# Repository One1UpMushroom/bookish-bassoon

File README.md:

# LED Task Lamp Controller

Firmware and a driver board for a five-channel LED task lamp (red, green, blue, warm
white, cool white), built from two 24 V LED strips and Adafruit breakout boards, and
controlled by a single push-button rotary encoder and a 240×240 color display.

| Part | Role |
|---|---|
| Adafruit **QT Py RP2040** | Microcontroller. Dual-core, 8 hardware PWM slices, 8 MB flash |
| Adafruit **I2C QT rotary encoder** (seesaw; PID 4991, or 5880 pre-soldered) | Encoder, push switch and an RGB "locator" pixel, all over I2C |
| Adafruit **240×240 TFT** (ST7789) | User interface |
| 1 m tunable-white strip (2700 K + 6500 K) and 0.8 m RGB strip, both 24 V | The light: about 15 W of white and 9 W of colour |
| **Driver board** ([`hardware/`](hardware/README.md)) | Carries the QT Py, makes its 5 V from the 24 V supply, and switches each strip colour with a MOSFET |

---

## 1. Wiring

```
                          QT Py RP2040
                   ┌─────────────────────────┐
     Red gate  ◄── │ A0  (GP29)    5V        │◄── 5 V from the board's buck converter
   Green gate  ◄── │ A1  (GP28)    GND       │── common ground
    Blue gate  ◄── │ A2  (GP27)    3V        │── TFT Vin, (encoder via STEMMA)
    Warm gate  ◄── │ A3  (GP26)    MO (GP3)  │──► TFT MOSI (SI)
     TFT TCS   ◄── │ SDA (GP24)    MI (GP4)  │◄── Encoder INT (extra wire)
     TFT D/C   ◄── │ SCL (GP25)    SCK (GP6) │──► TFT SCK
    Cool gate  ◄── │ TX  (GP20)    RX (GP5)  │──► TFT Lite (backlight PWM)
                   │   [STEMMA QT port]──────│──► Rotary encoder breakout
                   └─────────────────────────┘
```

| QT Py pad | GPIO | Connects to | Notes |
|---|---|---|---|
| A0 | GP29 | Red MOSFET gate (through 220 Ω) | PWM slice 6B |
| A1 | GP28 | Green MOSFET gate | PWM slice 6A |
| A2 | GP27 | Blue MOSFET gate | PWM slice 5B |
| A3 | GP26 | Warm white MOSFET gate | PWM slice 5A |
| TX | GP20 | Cool white MOSFET gate | PWM slice 2A |
| RX | GP5 | TFT **Lite** | PWM slice 2B: dimmable backlight |
| SCK | GP6 | TFT **SCK** | SPI0 |
| MO | GP3 | TFT **SI / MOSI** | SPI0 |
| MI | GP4 | Encoder breakout **INT** pad | Optional extra wire. Lets the firmware skip I2C reads while the knob is idle |
| SDA | GP24 | TFT **TCS** | Used as a plain GPIO |
| SCL | GP25 | TFT **D/C** | Used as a plain GPIO |
| STEMMA QT | GP22/23 | Encoder breakout | I2C1 (`Wire1`), 400 kHz |
| 3V / GND | | TFT Vin / GND | |
| 5V | | The board's 5 V buck converter (LMR33630), through a diode | USB may be connected at the same time |
| – | – | TFT **RST**, **CCS**, **SO**, **TE** | Leave unconnected. The display resets itself at power-up, and the microSD slot isn't used (leave it empty) |

On the driver board the LED pins and the 5 V feed are copper. The only wires are the
eight from the board's **J4** header (seven to the TFT, one to the encoder's INT pad),
the encoder's STEMMA QT cable, the 24 V supply and the two strips.

This uses all 11 pads, and every LED channel gets its own hardware PWM output.
If you don't run the INT wire, the firmware notices within a couple of knob turns and
falls back to plain polling. The pin
choice is deliberate: R+G and B+WW share PWM slices, so the firmware can phase-offset
them (see §5). Pin numbers live in `firmware/TaskLamp/config.h`.

**Encoder and I2C notes (from the Adafruit guides):**
* Clockwise turns increase values. The breakout's 45° encoder counts backwards, and the
  firmware compensates. *Settings ▸ Knob dir* flips it if your encoder differs.
* Touching the back of the encoder board can register as a button press. Insulate it
  from fingers and metal in the enclosure.
* Keep the STEMMA QT cable short (about 15 cm or less). Plug it in before powering up:
  I2C isn't designed for hot-plugging, although the firmware does retry every 2 s.
* With several encoders on one cable, Adafruit suggests powering their VIN separately
  if they misbehave.

**More controls without more pins:** the STEMMA QT port can be daisy-chained. A
**second rotary encoder breakout** with its A0 jumper cut (address 0x37) is detected
automatically. It becomes a dedicated **brightness knob**, and its click becomes
**power on/off**, working from any screen. This is the most worthwhile add-on for
day-to-day use. (The second knob has no INT wire, so it's simply polled.)

---

## 2. The driver board

The strips are never driven from the GPIO pins. The board in
[`hardware/`](hardware/README.md) does that, and also powers the QT Py from the lamp's
24 V supply:

* **24 V input**: a 2 A fuse, a Schottky diode against a supply wired backwards, a TVS
  diode against spikes, and bulk capacitors.
* **5 V for the QT Py** from an LMR33630 buck converter on the board (the BUCK//33630
  circuit), through a diode to the 5V pad. The 24 V input is the board's only power input.
  USB can be plugged in while the lamp is powered.
* **Five identical switches**: a logic-level MOSFET per colour (IRLB8721), its gate driven
  straight from the QT Py pin through 220 Ω, a 100 kΩ pull-down, and a 1N5819 from the
  strip wire back to +24 V.

`hardware/README.md` has the schematic, the files to send to PCBWay, the build order and
the power-up checks. [`docs/driver-build.html`](docs/driver-build.html) is the same build
as a step-by-step picture booklet. The parts not already in the inventory are listed with
links in [`docs/parts-to-order.md`](docs/parts-to-order.md).

What the firmware assumes about that hardware:

* **A high pin means light.** Each pin switches its MOSFET on directly.
* **The pull-downs keep the lamp dark** whenever the pins are not driven: during reset,
  in USB bootloader mode, or with the QT Py unplugged. The firmware then fades in rather
  than switching on hard.
* **PWM frequency.** The default is 2 kHz, under *Settings ▸ PWM freq* (500 Hz to 20 kHz).
  Lower frequencies dim further down; higher ones move any flicker beyond what a camera
  picks up. Resolution depends on frequency and on the CPU speed chosen in the Tools
  menu: 15–16 bits at 2 kHz, about 13 bits at 20 kHz.
* **The bottom of the dimming range.** A MOSFET gate driven through a resistor needs a
  fraction of a microsecond before the strip lights, so the very shortest pulses give no
  light. *Min duty* (§4) sets where light starts; the default is an estimate.
* **Currents.** The defaults are the catalogue figures for these strips: about 0.13 A per
  RGB colour and 0.30 A per white, 1.0 A with everything at 100 %.
* **The 3V rail** (QT Py regulator, 500 mA available) feeds the TFT and the encoder,
  tens of mA in total.
* **Display glass:** the 1.54" panel's backlight can slowly peel away from the TFT if
  nothing holds it. Plan a clear cover or window in the enclosure (or tape the edges).

---

## 3. Building and flashing

**Arduino IDE**
1. Boards Manager: install **Raspberry Pi Pico/RP2040** by Earle F. Philhower III.
2. Board: **Adafruit QT Py RP2040** (not the *Picoprobe* or *pico-debug* variants).
   *Flash Size*: pick an option **with** a filesystem (FS) of at least 64 KB. The default,
   "8MB (no FS)", leaves nowhere to store settings; the lamp then shows "No flash FS:
   settings not saved" on the home screen.
3. Library Manager: install **Adafruit seesaw Library**, **Adafruit ST7735 and ST7789 Library**
   and **Adafruit GFX Library**.
4. Open `firmware/TaskLamp/TaskLamp.ino` and upload. If the port doesn't appear, hold
   BOOT, tap RST, and keep holding BOOT until the RPI-RP2 drive appears.

**PlatformIO**: `pio run -t upload` (see `platformio.ini`).

**Host tests** (no hardware needed): `make -C test` runs about 4,100 checks of the
color math, light engine, power limiter, gesture decoder and the whole menu UI, including
a 200,000-event random-input fuzz run under AddressSanitizer/UBSan. `make -C test check`
also type-checks the Arduino-facing files against API stubs.

**Checked against the real toolchain:** the sketch compiles without warnings
(`-Wall -Wextra`) and links into a complete image with arduino-pico 6.3.2 (GCC 16.1),
Adafruit seesaw 1.7.9, Adafruit ST7735 and ST7789 1.12.0, Adafruit GFX 1.13.0 and Adafruit
BusIO 1.17.4. The image is about 392 KB of flash and 22 KB of static RAM.
`tools/rp2040_build_check.sh` repeats that build outside the Arduino IDE.

---

## 4. Using the lamp

### Gestures

| On the **home** screen | |
|---|---|
| **Turn** | Master brightness, 0.1–100 % on a perceptual scale. Steps are finer below 5 %, and spinning faster takes bigger steps |
| **Press + turn** | Quick parameter for the current mode: color temperature (White), hue (Color), speed (Sweep/Flash), period (Breathe/Rainbow), flicker (Candle) |
| **Click** | Open the menu. When the lamp is off: turn on |
| **Double-click** | Cycle through favorites |
| **Hold** (0.6 s) | Lamp on/off, with a smooth fade |

| In **menus** | |
|---|---|
| **Turn** | Move the selection, or change the value while editing |
| **Click** | Open a submenu, start editing a value, or confirm the edit |
| **Hold** | Go back. While editing: cancel and restore the old value |

When the screen is asleep, the first click only wakes it. Turning and holding work
immediately, so you can dim or switch off the lamp in the dark without looking.

### Modes

| Mode | What it does |
|---|---|
| **White** | Color temperature between your warm and cool LEDs, mixed in mired space for even steps |
| **Color** | Hue and saturation. The white part of pastel colors is produced by the white LEDs, which is more efficient and renders color better |
| **Mixer** | All five channels set independently |
| **Sweep** | Up to 8 programmable color steps, each with its own hold and fade time. Repeat, ping-pong or play once; linear or smooth easing; global speed 25–400 % |
| **Flash** | Color A/B flasher: on time, off time, flashes per burst, pause between bursts, speed. Hard-capped at 25 Hz |
| **Breathe** | Slow breathing of the base color, with an adjustable low point |
| **Rainbow** | Continuous hue rotation, with adjustable period and saturation |
| **Candle** | Natural-looking flicker of the base color |

*Breathe* and *Candle* animate the **base color**: the last White/Color/Mixer setting
you used. You can also change it in their *Adjust* menu. While you edit a sweep step or
a flash color, the lamp shows that color live. **Capture light** copies the current
base color into the step.

> ⚠️ Flashing light at 3–30 Hz can trigger seizures in people with photosensitive
> epilepsy. Use the Flash mode with care.

### Menu map

```
Menu
├── Mode ▸ White · Color · Mixer · Sweep · Flash · Breathe · Rainbow · Candle
├── Adjust ▸ (parameters of the current mode; Sweep ▸ Steps ▸ Step n ▸ R G B Warm Cool Hold Fade)
├── Favorites ▸ recall 1-6 · Save current ▸ slot 1-6
├── Sleep: Off / 5 / 15 / 30 / 60 / 90 min / 2 hr (fades out over the last 5 min)
└── Settings
    ├── Transition (fade time for on/off and mode changes)
    ├── White LEDs ▸ Warm LED K · Cool LED K · Max output · Pastel->W
    ├── Display ▸ Brightness · Follow lamp · Timeout · Knob glow
    ├── Knob dir
    ├── Power ▸ Budget · R/G/B/WW/CW current at 100 %
    ├── Channels ▸ Red/Green/Blue/Warm/Cool ▸ Test level · Min duty · Trim
    ├── PWM freq
    ├── Factory reset
    └── Firmware
```

### One-time calibration (recommended)

1. **Channels ▸ each channel**: on this screen the lamp shows *only* that channel at the
   *Test level* (default 0.1 %). Test and preview screens stay up for 10 minutes instead of
   the usual 30 s, so there is time to take a meter reading.
   * Set **Min duty** so the strip just glows at the test level: lower it until the light
     goes out, then back up one step. The defaults (0.12 % for red, 0.16 % for the others)
     come from simulating the driver board. This puts the dimmest real light on the first
     step of the knob.
   * Use **Trim** to cap a channel. This is useful for balancing the warm and cool whites.
2. **White LEDs**: the color temperatures of the warm and cool LEDs. The defaults, 2700 K
   and 6500 K, match the strip in this build.
3. **Power**: the defaults are catalogue figures. Measure each channel's current at 100 %
   and enter it, then set **Budget** to about 80 % of your supply's rating. The home
   screen shows the estimated current draw. Above the budget, all channels are scaled
   down together, so the color stays the same, and the header shows **LIMIT**.
4. **PWM freq**: leave it at 2 kHz unless a camera shows banding (raise it) or you want
   deeper dimming (lower it). Changing it moves the *Min duty* point, so redo step 1.

---

## 5. How the firmware works (and why it's efficient)

```
 core 0 ─ UI ──────────────────────────────┐       core 1 ─ light ───────────────────────────┐
 encoder (I2C, error-checked) → gestures   │       LightEngine: mode/effect → linear RGBWW    │
 → menus/home → Settings + Runtime ────────┼─copy─►  soft start, crossfade, sleep fade        │
 display (banded, change-only)             │       OutputStage: trim → power cap → min duty │
 flash save (debounced, atomic)            │◄──────  PwmBank: 16-bit HW PWM, phase-staggered│
 watchdog (fed only if both cores alive)   │status   backlight glide                         │
```

* **Two cores.** Core 1 does nothing but compute light and write PWM, so fades and
  effects stay smooth while the display redraws. The cores exchange one snapshot each way.
  The mutex is held only for a copy, and core 1 never waits on it. The one thing that does
  pause core 1 is a flash write: the RP2040 can't run code from flash while erasing it, so
  the core is held for a few tens of ms. The hardware PWM keeps running, so a steady light
  shows nothing. See *Flash wear* for how effects are kept clear of it.
* **Perceptual control, linear mixing.** Every level you set is CIE L\* lightness, so
  equal knob steps look equal from 0.1 % to 100 %. Mixing and cross-fading happen in
  linear light, which is how LED light physically adds up.
* **Deep, smooth dimming.** Hardware PWM runs at the highest resolution the chosen
  frequency allows, and the per-channel *Min duty* floor puts the bottom of the knob
  exactly where each strip starts to emit.
* **Less stress on the power supply.** The three PWM slices start a third of a period
  apart, and the second channel in each slice is end-aligned. Channels therefore don't
  all switch on at the same instant, which lowers peak current, ripple and EMI. Every
  on/off and mode change ramps instead of stepping, so there are no inrush spikes. The
  power budget keeps total current inside what your supply can deliver.
* **Low idle power.** The engine ticks at 250 Hz only while something is changing, and
  drops to 50 Hz when the light is steady. PWM registers are written only when a value
  changes. The display is drawn into a 23 KB band buffer, and each band is hashed: bands
  that didn't change are never sent over SPI. A brightness change typically re-sends 1–2
  of the 5 bands. The backlight follows the lamp's brightness (less glare at night),
  dims after the timeout and sleeps 10 s later. The display controller then enters its
  sleep mode. The QT Py's own NeoPixel is left unpowered. When the lamp is off, a faint
  amber glow on the encoder shows where the knob is.
* **Flash wear.** Settings are saved only after 5 s without changes, and only if they
  differ (by CRC) from what's stored. While an effect is running the wait is 30 s, or
  until the light is steady or off, so the short pause a flash write causes doesn't land
  in the middle of a sweep. The write goes through LittleFS (wear-levelled), to
  a temporary file followed by an atomic rename, so a power cut can't corrupt them. On
  load, the data is CRC-checked and every field is range-clamped.
* **Interrupt-driven input.** With INT wired, an idle knob costs one GPIO read per poll.
  I2C is used only when the encoder signals a change, while the button is held, for half
  a second after activity, and in a 4 Hz safety poll. An edge latch catches even short
  INT pulses.
* **Robust input.** Encoder reads check for I2C errors, so a loose cable can't look like
  a held button. A missing encoder is retried every 2 s. The switch is debounced, and the
  hardware watchdog reboots the board if either core ever stalls.
* **Clean power-up.** The backlight is held dark until the first frame is ready, so the
  display's power-up noise is never shown.
* **Display sleep timing.** The ST7789 needs 120 ms between going to sleep and waking, and
  5 ms before its next command. The driver enforces both, so touching the knob at the
  instant the screen dozes off can't leave it dark.

### Source map (`firmware/TaskLamp/`)

| File | Contents | Hardware-free? |
|---|---|---|
| `TaskLamp.ino` | Startup, core 0/core 1 loops, encoder I/O | – |
| `config.h` | Pins and timing | ✓ |
| `color.*` | CIE lightness, HSV, CCT mixing | ✓ |
| `settings.*` | Persistent settings, defaults, sanitizing, CRC, save scheduler | ✓ |
| `engine.*` | Modes, effects, fades, sleep timer, previews | ✓ |
| `output.*` | Trim, power budget, duty floor → PWM levels | ✓ |
| `input.*` | Click / double / long / press-turn gestures, acceleration, INT gating | ✓ |
| `ui.*` | Home screen, menu system, display power policy | ✓ |
| `painter.h` | Drawing interface used by the UI | ✓ |
| `display.*` | ST7789 driver, banded change-only rendering | – |
| `pwm_hw.*` | RP2040 PWM setup and phase staggering | – |
| `storage.*` | LittleFS load/save | – |

Outside the firmware: `hardware/` (the driver board's KiCad project and factory files),
`tools/pcb/` (the generator and checks that produce it) and `tools/rp2040_build_check.sh`
(full build with the real core and libraries).

---

## 6. Status

* All hardware-independent logic is covered by the host tests (`make -C test`).
* The whole sketch builds and links cleanly with the real arduino-pico toolchain and the
  current Adafruit libraries (§3). That was last run on 1.2.0; 1.2.1 changes only default
  values, and the host tests compile it.
* Firmware 1.1 ran on a breadboard build: the display, the encoder and the two white
  channels worked there. **Firmware 1.2.1 has not yet been run on hardware.** It differs
  in its defaults and in dropping one menu option, not in how it drives the pins.
* The driver board passes KiCad's design-rule check, 20 circuit simulations and 22 checks
  of its factory files (`hardware/tasklamp-driver/test-report.md`), but **no board has been
  built yet**. Its power-up section lists
  what to measure on the first one.
* Still worth confirming on the bench:
  * Clockwise turns brighten. If not, use *Knob dir*.
  * The display orientation (`kTftRotation` in `config.h`).
  * INT works: the encoder's red INT LED (on the back) blinks when you turn the knob.
  * No white flash on the display at power-up.

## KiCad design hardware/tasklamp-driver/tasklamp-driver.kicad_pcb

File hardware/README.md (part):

# Task lamp driver board

One circuit board that turns a 24 V supply and a QT Py RP2040 into a five-channel strip
lamp: 0.8 m of RGB tape and 1 m of tunable-white tape, each colour switched by its own
MOSFET.

| | |
|---|---|
| Size | 96.5 × 59 mm, two layers, 1.6 mm |
| Mounting | Four 3.2 mm holes (M3) on a 88.9 × 50.8 mm (3.5 × 2.0 in) rectangle |
| Supply | 24 V DC, 1.5 A or more. About 1.0 A is drawn with every channel at 100 % |
| Outputs | Red, green, blue: about 0.13 A each. Warm white, cool white: about 0.30 A each |
| Controller power | 5 V made on the board from the 24 V input; USB can be plugged in at the same time |
| Parts | Through-hole, except the 5 V converter's eleven surface-mount parts (hand-solderable). Most are in the inventory; fifteen lines to buy ([`docs/parts-to-order.md`](../docs/parts-to-order.md)) |
| Power input | One: 24 V into J1. Everything on the board, the QT Py included, runs from it |

## What is on it

```
 24 V in ─ fuse ─ Schottky ─┬───────────────┬──────────────── +24 V to both strips
          (2 A)  (reverse   │               │
                 protection)│               └─ 5 V buck (LMR33630) ─ diode ─ QT Py 5V pad
                           TVS, 2 × 100 µF

 QT Py pin ── 220 Ω ──┬── gate ┐
                    100 kΩ     │ IRLB8721      × 5: red, green, blue, warm, cool
                      │   source ── ground
                    ground  drain ── strip colour wire, and a 1N5819 up to +24 V
```

* **Input.** Fuse first, then a Schottky diode so a supply wired backwards reaches nothing,
  then a TVS diode and two bulk capacitors on the 24 V rail.
* **5 V supply.** An LMR33630 buck converter, the circuit of the BUCK//33630 breakout set
  for 5.02 V, feeds the QT Py's 5V pad
  through a diode. The QT Py has its own diode from USB, so either source, or both, can
  be connected.
* **Five identical switches.** The QT Py pin drives the MOSFET gate through 220 Ω. The
  100 kΩ pull-down keeps the strip dark whenever the pin is not driving: during reset,
  while a new program loads, or with the QT Py unplugged. The 1N5819 returns the kick
  from the strip wiring to the rail when the MOSFET turns off.
* **Display header.** Seven wires to the TFT and one to the encoder's INT pad. The encoder
  itself plugs into the QT Py's STEMMA QT socket.

The full schematic is [`tasklamp-driver-schematic.pdf`](tasklamp-driver/tasklamp-driver-schematic.pdf)
([picture](tasklamp-driver/img/schematic.png)).

## Files

| File | What it is |
|---|---|
| `tasklamp-driver/tasklamp-driver-gerbers.zip` | **Upload this to PCBWay.** Seven Gerber layers and two drill files |
| `tasklamp-driver/tasklamp-driver.kicad_pro` | The KiCad project (KiCad 7 or newer): schematic and board, editable |
| `tasklamp-driver/tasklamp-driver-schematic.pdf` | Schematic |
| `tasklamp-driver/tasklamp-driver-bom.csv` | Every part, with where it comes from |
| `tasklamp-driver/gerbers/` | The same factory files unzipped, plus drill maps |
| `tasklamp-driver/img/` | Pictures of both sides, rendered from the Gerber files |
| `tasklamp-driver/test-report.md` | **What was tested and what it showed**: circuit simulations and checks of the factory files |
| `tasklamp-driver/sim/` | Simulation results (`results.json`) and plots |
| `tasklamp-driver/board-tests.json` | Results of the factory-file checks |

## Ordering the boards from PCBWay

1. On pcbway.com choose **PCB Instant Quote** and upload
   `tasklamp-driver-gerbers.zip`. The size (96.5 × 59 mm) and layer count (2) are read
   from the file.
2. Keep FR-4, 1.6 mm and 1 oz copper, and set these for the board's look (Neon Noir
   Chartreuse, revision C):

   | Option | Choose |
   |---|---|
   | Solder mask | **Matte black** (plain black if matte isn't offered) |
   | Silkscreen | **White** |
   | Surface finish | **ENIG** |

   Black mask and ENIG cost more than green and HASL; the quote shows the difference.
   The circuit works the same with any colour and finish, so green with HASL is fine if
   you'd rather save it. Nothing needs a special process: the narrowest track is 0.4 mm,
   the closest copper 0.23 mm apart (in the converter), the smallest hole 0.4 mm (18 ground
   vias round the converter).
3. Quantity 5 is the minimum and usually the cheapest tier.
4. Look at PCBWay's own preview before paying. It should look like the two pictures in
   `tasklamp-driver/img/`.

With green and HASL, expect about $5 for the boards plus shipping. US orders also pay
import duty, collected at checkout; see [`docs/pcb-planning.md`](../docs/pcb-planning.md)
for the alternatives (OSH Park makes boards in the US from the same files, with ENIG as
standard).

## Building it

The same steps, with a picture of the board for each one, are in the build booklet:
[`docs/driver-build.html`](../docs/driver-build.html).

Solder the converter's surface-mount parts first, while the board is bare, then the low
through-hole parts so the board lies flat. Every through-hole position has its value
printed inside the outline.

| Step | Parts | Which way round |
|---|---|---|
| 1 | The 5 V converter, surface-mount: U2 **LMR33630**, L1 **10 µH**, C8–C11 **22 µF**, C3–C4 **10 µF**, C5 **220 nF**, R12 **24.9 kΩ**, R11 **100 kΩ** | Only the chip has a right way round: its dot to the top left. Solder one corner pin, check it's straight, then the rest; fill the hole in its centre pad with solder from the back. Values aren't printed on the board: use the booklet's step 1 picture |
| 2 | R1–R5, **220 Ω** (red, red, black, black, brown) | Either way |
| 3 | R6–R10, **100 kΩ** (brown, black, black, orange, brown) | Either way |
| 4 | D1–D6, **1N5819** | Stripe toward the **K** mark and the band on the outline |
| 5 | D7 **SB560** and D8 **P6KE30A** | Stripe toward **K** |
| 6 | C6 **100 nF** (marked 104) and C7 **1 µF** (105), right of the converter chip | Either way |
| 6 | Two **1×7 sockets** and the 8-pin header J4 | Plug the sockets onto the QT Py's pins first and solder them with the QT Py in place, so they end up straight and parallel |
| 7 | Fuse holder F1, screw terminals J1, J2, J3 | Wire openings toward the board edge |
| 8 | C1, C2 **100 µF** | Long lead in the hole marked **+**. The stripe on the can goes over the filled half of the circle |
| 9 | Q1–Q5, **IRLB8721**, the five picked below | Metal tab toward the resistors, printing toward the screw terminals. The outline has a second line on the tab side |

The IRLB8721 shares its package with other parts in the inventory (IRFZ44N, the 78xx
regulators). Read the printing on each one: only IRLB8721 goes in Q1–Q5.

### Picking the five MOSFETs

The gates are driven from 3.3 V, and the IRLB8721's datasheet only guarantees full
conduction at 4.5 V. For a typical part that doesn't matter: it is fully on with a large
margin. The simulation (see the test report) shows that a part at the very top of the
datasheet's threshold range would still be on in a warm room, but in a cold one its margin
could shrink to almost nothing. There are 19 in the inventory and the board takes five, so
pick the best five first. It takes a few minutes:

1. Clip the **gate and drain** (the left and middle legs, printing toward you) together.
2. **9 V battery +** through a **1 kΩ** resistor to those two legs; **battery −** to the
   right leg (source).
3. Measure from the left leg to the right leg. A typical part reads **about 2.0–2.2 V**.
4. Measure them all, fit the **five lowest**, and set aside any that read **above 2.6 V**.
   A part reading 2.6 V or less keeps at least 0.1 V of margin even at 0 °C.

## First power-up

Do these in order. Each one protects the step after it.

1. **Nothing plugged in: no QT Py, no strips, no display.** Fit the fuse and connect 24 V
   to J1 (**+** and **−** are printed beside it, and on the back).
   * Between **+24** on either strip terminal and the **GND** test pad: about 23.5 V
     (the supply less the Schottky's drop).
   * Between the **+5V** and **GND** test pads: 4.9 to 5.1 V.
     If this is wrong, stop. Anything else here would put the wrong voltage on the QT Py.
2. **Strips connected, still no QT Py.** Nothing may light. The pull-downs are holding
   every MOSFET off.
3. **Power off. Plug in the QT Py**, USB socket toward the board edge, and connect the
   display and encoder. Power on: the display starts and the lamp fades up.
4. **One colour at a time.** In *Settings ▸ Channels*, open each channel in turn. Only
   that colour may light. If a different colour lights, two wires are swapped at the
   terminal.
5. **Are the MOSFETs fully on?** Set a channel to 100 % (Mixer mode) and measure from that
   colour's screw terminal to the GND test pad: it must read **under 0.1 V**. Simulated, a
   typical part reads about 0.004 V. This is the check that matters, because the datasheet
   only guarantees 4.5 V drive. A channel that reads higher gets another IRLB8721 from the
   bag.
   With that colour **off**, the same screw reads anything from about 5 V up to 24 V: the
   strip's LEDs hold back part of the 24 V. Only 0 V means a fault (a bridge at the MOSFET).
6. **Calibrate** as the main README describes: *Min duty* per channel, then measured
   currents under *Power*. The Min duty defaults, 0.12 % for red and 0.16 % for the other
   colours, come from simulating this board, so the right setting should be near them.

## Wiring

| Terminal | Goes to |
|---|---|
| **24V IN +, −** | The 24 V supply |
| **RGB STRIP +24, R, G, B** | The RGB tape's four wires. Match the letters printed on the tape at the cut line; wire colours vary |
| **WHITE STRIP +24, WW, CW** | The tunable-white tape's three wires: its common +, warm, cool |
| **J4: 3V, GND, SCK, MOSI, CS, DC, LITE** | TFT pads Vin, GND, SCK, SI, TCS, D/C, Lite |
| **J4: INT** | The encoder board's INT pad |
| QT Py STEMMA QT socket | The encoder board, with its own cable |

Cut the tapes only at the marked copper pads: every 100 mm on the RGB tape, so 800 mm is
eight segments.

## How the board was checked

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
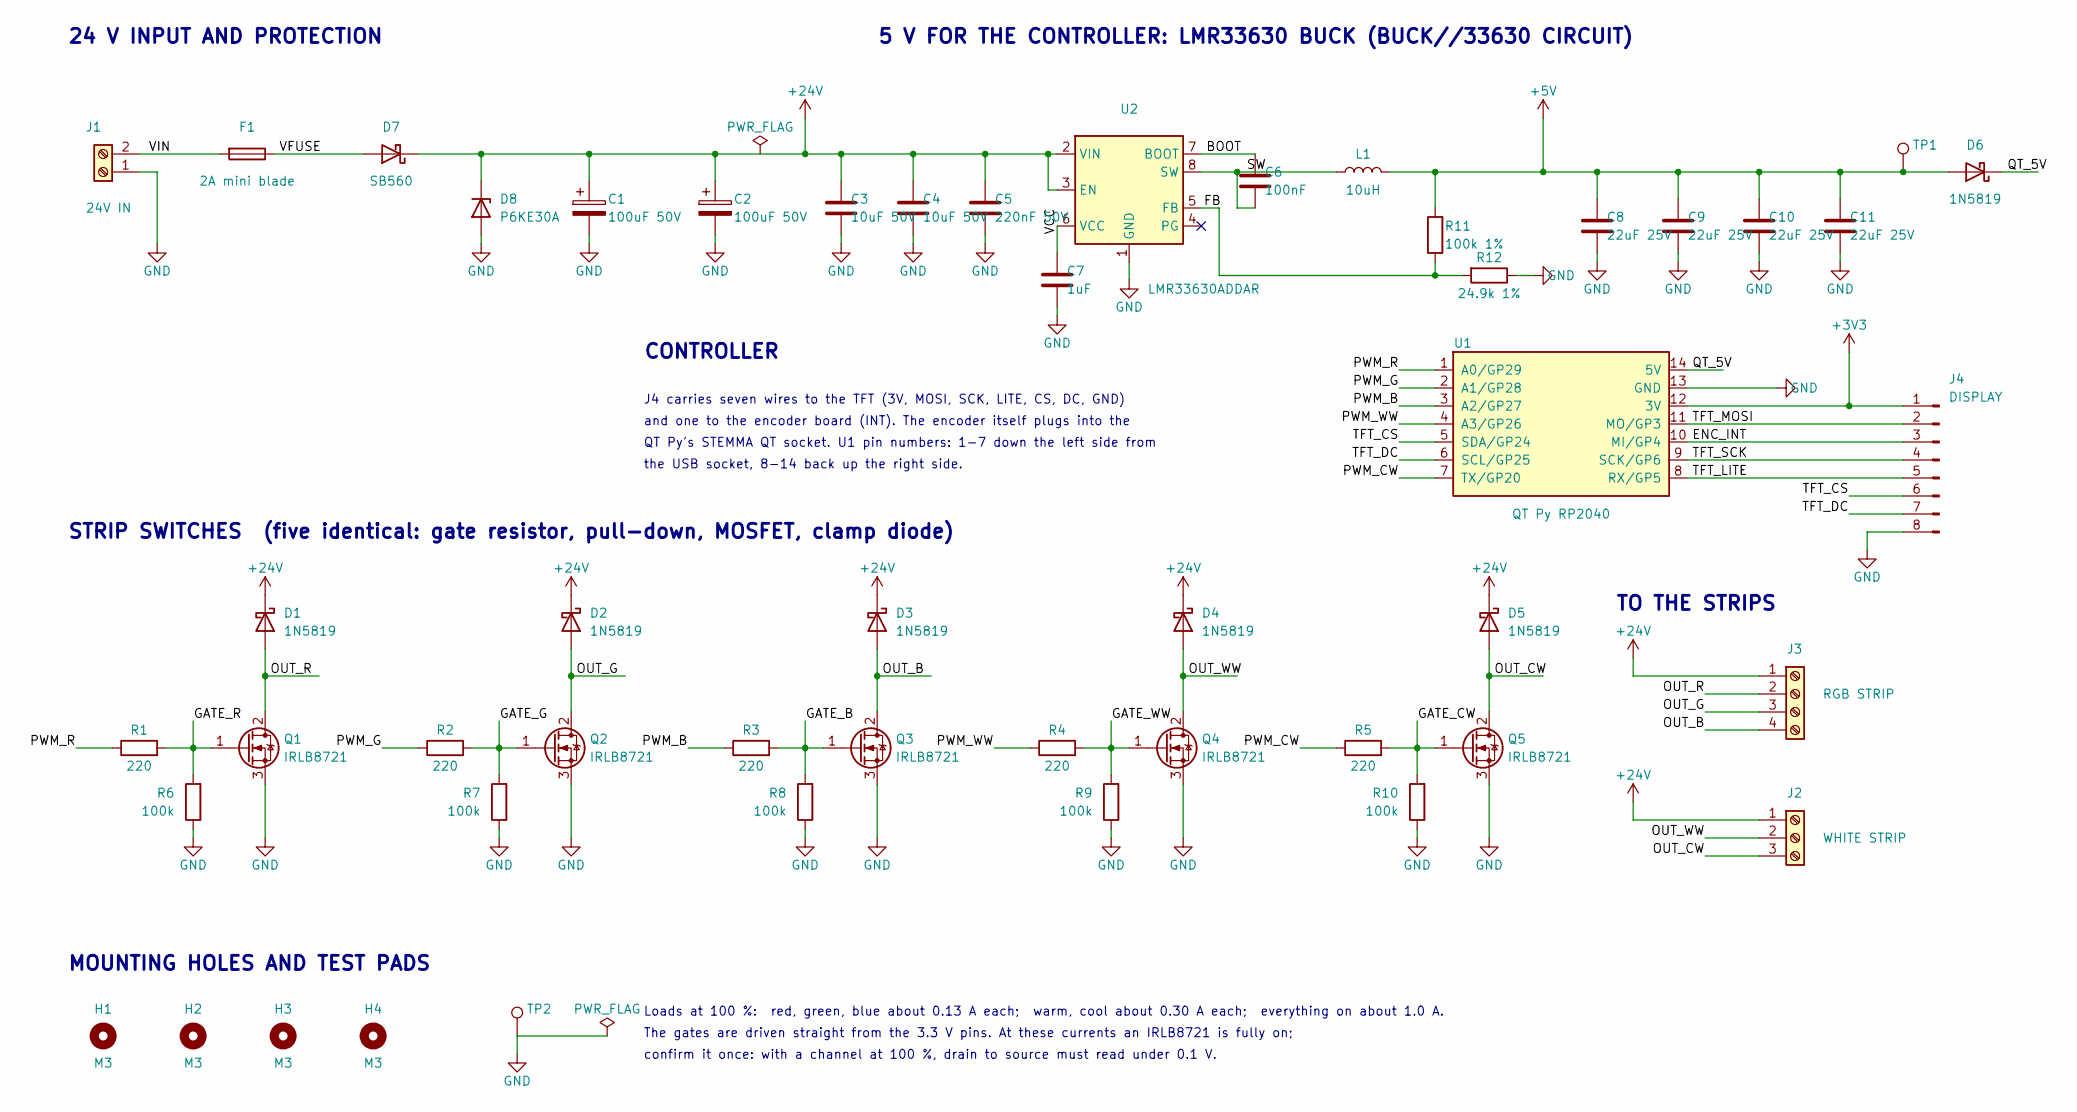
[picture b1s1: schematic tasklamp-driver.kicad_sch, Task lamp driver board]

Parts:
C1, C2: 100uF 50V; CP_Radial_D8.0mm_P3.50mm
C3, C4: 10uF 50V; C_1210_HandSolder; MPN GRM32ER71H106KA12L
C5: 220nF 50V; C_0805-1206_HandSolder; MPN C0805C224K5RACTU
C6: 100nF; C_Dual_THT-P5.08_or_0805-1206
C7: 1uF; C_Dual_THT-P5.08_or_0805-1206
C8, C9, C10, C11: 22uF 25V; C_1210_HandSolder; MPN GRM32ER71E226KE15L
D1, D2, D3, D4, D5, D6: 1N5819; D_DO-41_SOD81_P10.16mm_Horizontal
D7: SB560; D_DO-201AD_P15.24mm_Horizontal; MPN SB560-E3/54
D8: P6KE30A; D_DO-15_P12.70mm_Horizontal; MPN P6KE30A
F1: 2A mini blade; Fuseholder_Blade_Mini_Keystone_3568; MPN 3568 + 0297002.WXNV
H1, H2, H3, H4: M3; MountingHole_3.2mm_M3
J1: 24V IN; TerminalBlock_Phoenix_MKDS-1,5-2-5.08_1x02_P5.08mm_Horizont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; MPN OSTTC022162
J2: WHITE STRIP; TerminalBlock_Phoenix_MKDS-1,5-3-5.08_1x03_P5.08mm_Horizont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; MPN OSTTC032162
J3: RGB STRIP; TerminalBlock_Phoenix_MKDS-1,5-4-5.08_1x04_P5.08mm_Horizont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; MPN OSTTC042162
J4: DISPLAY; PinHeader_1x08_P2.54mm_Vertical
L1: 10uH; L_Bourns_SRP7028A_HandSolder; MPN SRP7028A-100M
Q1, Q2, Q3, Q4, Q5: IRLB8721; TO-220-3_Vertical
R1, R2, R3, R4, R5: 220; R_Axial_DIN0207_L6.3mm_D2.5mm_P10.16mm_Horizontal
R6, R7, R8, R9, R10: 100k; R_Axial_DIN0207_L6.3mm_D2.5mm_P10.16mm_Horizontal
R11: 100k 1%; R_0805-1206_HandSolder; MPN RC1206FR-07100KL
R12: 24.9k 1%; R_0805-1206_HandSolder; MPN RC1206FR-0724K9L
TP1: +5V; TestPoint_THTPad_D2.0mm_Drill1.0mm
TP2: GND; TestPoint_THTPad_D2.0mm_Drill1.0mm
U1: QT Py RP2040; QTPy_RP2040_Socket; MPN 2x PPTC071LFBN-RC
U2: LMR33630ADDAR; HSOIC-8-1EP_HandSolder_BackHole; MPN LMR33630ADDAR

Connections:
+3V3: J4.1, U1.12 (3V)
+5V: C8.1, C9.1, C10.2, C11.2, D6.2 (A), L1.2, R11.2, TP1.1
+24V: C1.1, C2.1, C3.2, C4.1, C5.2, D1.1 (K), D2.1 (K), D3.1 (K), D4.1 (K), D5.1 (K), D7.1 (K), D8.1 (K), J2.1, J3.1, U2.2 (VIN), U2.3 (EN)
BOOT: C6.2, U2.7 (BOOT)
ENC_INT: J4.3, U1.10 (MI/GP4)
FB: R11.1, R12.2, U2.5 (FB)
GATE_B: Q3.1 (G), R3.2, R8.2
GATE_CW: Q5.1 (G), R5.2, R10.2
GATE_G: Q2.1 (G), R2.2, R7.2
GATE_R: Q1.1 (G), R1.2, R6.2
GATE_WW: Q4.1 (G), R4.2, R9.2
GND: C1.2, C2.2, C3.1, C4.2, C5.1, C7.2, C8.2, C9.2, C10.1, C11.1, D8.2 (A), J1.1, J4.8, Q1.3 (S), Q2.3 (S), Q3.3 (S), Q4.3 (S), Q5.3 (S), R6.1, R7.1, R8.1, R9.1, R10.1, R12.1, TP2.1, U1.13 (GND), U2.1 (GND), U2.9 (GND)
OUT_B: D3.2 (A), J3.4, Q3.2 (D)
OUT_CW: D5.2 (A), J2.3, Q5.2 (D)
OUT_G: D2.2 (A), J3.3, Q2.2 (D)
OUT_R: D1.2 (A), J3.2, Q1.2 (D)
OUT_WW: D4.2 (A), J2.2, Q4.2 (D)
PWM_B: R3.1, U1.3 (A2/GP27)
PWM_CW: R5.1, U1.7 (TX/GP20)
PWM_G: R2.1, U1.2 (A1/GP28)
PWM_R: R1.1, U1.1 (A0/GP29)
PWM_WW: R4.1, U1.4 (A3/GP26)
QT_5V: D6.1 (K), U1.14 (5V)
SW: C6.1, L1.1, U2.8 (SW)
TFT_CS: J4.6, U1.5 (SDA/GP24)
TFT_DC: J4.7, U1.6 (SCL/GP25)
TFT_LITE: J4.5, U1.8 (RX/GP5)
TFT_MOSI: J4.2, U1.11 (MO/GP3)
TFT_SCK: J4.4, U1.9 (SCK/GP6)
VCC: C7.1, U2.6 (VCC)
VFUSE: D7.2 (A), F1.1
VIN: F1.2, J1.2

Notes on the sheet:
24 V INPUT AND PROTECTION
5 V FOR THE CONTROLLER: LMR33630 BUCK (BUCK//33630 CIRCUIT)
CONTROLLER
J4 carries seven wires to the TFT (3V, MOSI, SCK, LITE, CS, DC, GND)
and one to the encoder board (INT). The encoder itself plugs into the
QT Py's STEMMA QT socket. U1 pin numbers: 1-7 down the left side from
the USB socket, 8-14 back up the right side.
STRIP SWITCHES (five identical: gate resistor, pull-down, MOSFET, clamp diode)
TO THE STRIPS
MOUNTING HOLES AND TEST PADS
Loads at 100 %: red, green, blue about 0.13 A each; warm, cool about 0.30 A each; everything on about 1.0 A.
The gates are driven straight from the 3.3 V pins. At these currents an IRLB8721 is fully on;
confirm it once: with a channel at 100 %, drain to source must read under 0.1 V.

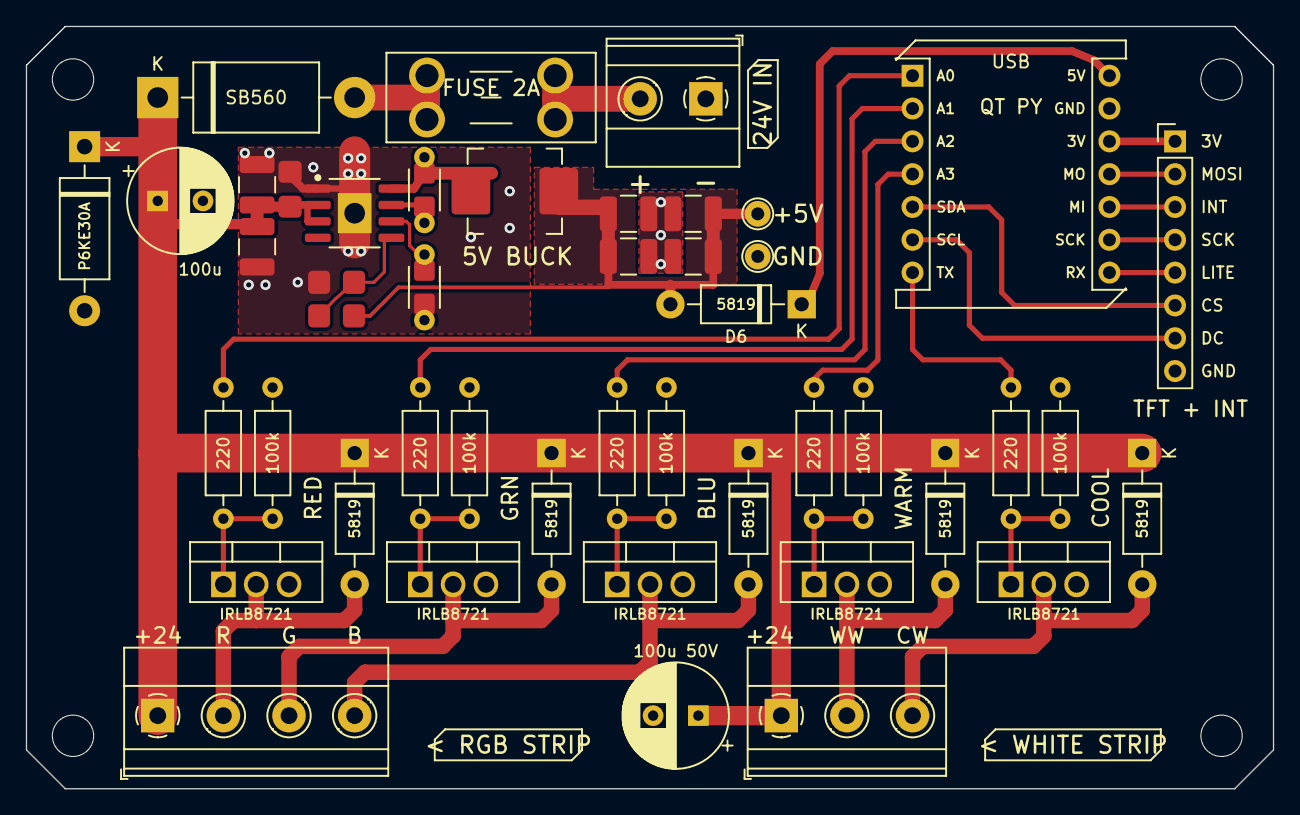
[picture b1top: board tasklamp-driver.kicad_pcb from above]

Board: 2 copper layers, 96.5 x 59.0 mm, 50 parts (0 on the bottom side), 32 nets.

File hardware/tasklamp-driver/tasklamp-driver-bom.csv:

Qty,References,Value,What it is,From,Part number,Footprint
1,J1,24V IN,"24 V supply input, 5.08 mm screw terminal",to order,OSTTC022162,"TerminalBlock_Phoenix_MKDS-1,5-2-5.08_1x02_P5.08mm_Horizontal"
1,J2,WHITE STRIP,"Tunable-white strip: +24 V, warm, cool",to order,OSTTC032162,"TerminalBlock_Phoenix_MKDS-1,5-3-5.08_1x03_P5.08mm_Horizontal"
1,J3,RGB STRIP,"RGB strip: +24 V, red, green, blue",to order,OSTTC042162,"TerminalBlock_Phoenix_MKDS-1,5-4-5.08_1x04_P5.08mm_Horizontal"
1,J4,DISPLAY,Pin header to the TFT and the encoder INT pad,in stock,,PinHeader_1x08_P2.54mm_Vertical
1,F1,2A mini blade,Mini (ATM) blade fuse holder with a 2 A fuse,to order,3568 + 0297002.WXNV,Fuseholder_Blade_Mini_Keystone_3568
1,U1,QT Py RP2040,Adafruit QT Py RP2040 on two 1x7 sockets (the board itself is on hand),"board in stock, sockets to order",2x PPTC071LFBN-RC,QTPy_RP2040_Socket
1,U2,LMR33630ADDAR,"24 V to 5 V buck converter, 3 A, 400 kHz",to order,LMR33630ADDAR,HSOIC-8-1EP_HandSolder_BackHole
5,Q1 Q2 Q3 Q4 Q5,IRLB8721,Strip switch,in stock,,TO-220-3_Vertical
1,L1,10uH,"Buck inductor, shielded, Isat 6 A",to order,SRP7028A-100M,L_Bourns_SRP7028A_HandSolder
5,D1 D2 D3 D4 D5,1N5819,Clamp for the strip wiring,in stock,,D_DO-41_SOD81_P10.16mm_Horizontal
1,D6,1N5819,Feeds the QT Py 5V pad; lets USB be plugged in at the same time,in stock,,D_DO-41_SOD81_P10.16mm_Horizontal
1,D7,SB560,"Reverse-polarity protection, 60 V 5 A Schottky",to order,SB560-E3/54,D_DO-201AD_P15.24mm_Horizontal
1,D8,P6KE30A,Surge clamp (TVS) across the 24 V rail,to order,P6KE30A,D_DO-15_P12.70mm_Horizontal
5,R1 R2 R3 R4 R5,220,Gate resistor,in stock,,R_Axial_DIN0207_L6.3mm_D2.5mm_P10.16mm_Horizontal
5,R6 R7 R8 R9 R10,100k,Gate pull-down,in stock,,R_Axial_DIN0207_L6.3mm_D2.5mm_P10.16mm_Horizontal
1,R11,100k 1%,"Feedback divider, top (0805 or 1206)",to order,RC1206FR-07100KL,R_0805-1206_HandSolder
1,R12,24.9k 1%,"Feedback divider, bottom: 5.02 V out (0805 or 1206)",to order,RC1206FR-0724K9L,R_0805-1206_HandSolder
1,C1,100uF 50V,Bulk capacitor at the input,in stock,,CP_Radial_D8.0mm_P3.50mm
1,C2,100uF 50V,Bulk capacitor beside the strip terminals,in stock,,CP_Radial_D8.0mm_P3.50mm
2,C3 C4,10uF 50V,"Buck input capacitor, X7R",to order,GRM32ER71H106KA12L,C_1210_HandSolder
1,C5,220nF 50V,"Buck input bypass, X7R 0805 or 1206",to order,C0805C224K5RACTU,C_0805-1206_HandSolder
1,C6,100nF,"Bootstrap capacitor (radial, or a chip on the inner pads)",in stock,,C_Dual_THT-P5.08_or_0805-1206
1,C7,1uF,"Buck VCC capacitor (radial, or a chip on the inner pads)",in stock,,C_Dual_THT-P5.08_or_0805-1206
4,C8 C9 C10 C11,22uF 25V,"Buck output capacitor, X7R",to order,GRM32ER71E226KE15L,C_1210_HandSolder

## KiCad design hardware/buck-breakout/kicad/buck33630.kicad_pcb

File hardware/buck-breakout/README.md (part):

# BUCK//33630: adjustable 3 A buck converter breakout

A small step-down converter board built around the **TI LMR33630ADDAR**. One board
design covers every output from 3.3 V to 24 V; you pick the voltage at assembly
time by fitting the resistors and inductor listed on the back of the board.

| | |
|---|---|
| Input | 3.8 V to 36 V (38 V absolute maximum) |
| Output | 1 V to 24 V, set by resistors. Table for 3.3, 5, 9, 12 and 24 V |
| Current | 3 A (see [Heat](#heat-and-efficiency) for continuous use) |
| Type | Synchronous buck, 400 kHz, internally compensated |
| Standby | Tens of microamps with no load (24 µA in the chip plus the feedback divider) |
| Board | 48.26 × 22.86 mm (1.9 × 0.9 in), 2 layers, parts on one side |
| Breadboard | Two rows of pins 0.8 in apart, 10 pins |
| Panel | 2 × 4 boards, 98.5 × 97.4 mm, snap apart by hand |

**Status: designed and rule-checked, not yet built.** Both board files pass KiCad's
design-rule check with no violations, and the fabrication files are ready to order.
Nothing here has been soldered or measured, so treat the first panel as the
prototype. [What to check on the first board](#bring-up) is listed below.

---

## Two limits to know before building

**A buck converter only steps down.** The output is always lower than the input,
so not every combination in "3.3 to 24 V out from 5 to 24 V in" is possible:

| You want | You need |
|---|---|
| 3.3 V | 4.5 V in or more |
| 5 V | 6 V in or more |
| 9 V | 10 V in or more |
| 12 V | 13 V in or more. A 12 V battery sags below that, so the output just follows the battery, about 0.2–0.4 V lower |
| 24 V | **28 to 36 V in.** From a 24 V supply you get roughly 23.5 V, unregulated |

If a project needs 24 V from 12 V, or a steady 12 V from a vehicle battery, that
calls for a boost or buck-boost converter: a different chip and board.

**36 V is the ceiling.** That covers 5, 12 and 24 V supplies and 12 V vehicles
(with the fuse and TVS diode described under [Vehicle use](#vehicle-use)). It does
not cover 24 V truck electrics, 36 V or 48 V battery packs.

---

## Why the LMR33630

Requirements: adjustable 3.3–24 V out, 5–24 V in, hand-solderable, and the best mix
of efficiency, performance and cost from what DigiKey stocks.

| Part | Input | Current | Type | Package | Verdict |
|---|---|---|---|---|---|
| **TI LMR33630ADDAR** | 3.8–36 V | 3 A | Synchronous, 400 kHz | HSOIC-8, 1.27 mm pitch | **Chosen** |
| TI LMR51430 | 4.5–36 V | 3 A | Synchronous | SOT-23-6 | Cheaper (about \$1.60), but the tiny package is harder to solder and sheds heat poorly at 3 A |
| TI LMR38020 | 4.2–80 V | 2 A | Synchronous | HSOIC-8 | Good for 48 V systems. Costs more (about \$3) for less current |
| TI TPS54360B | 4.5–60 V | 3.5 A | Non-synchronous | HSOIC-8 | Needs an external diode and a compensation network; lower efficiency |
| TI LM2596 | 4.5–40 V | 3 A | Non-synchronous, 150 kHz | TO-220 / TO-263 | Easiest to solder, but 10 or more points less efficient at 3.3–5 V, 5 mA standby, and needs a much larger inductor |

What decided it:

* **The output range is exactly the one asked for.** The datasheet rates it for
  1 V to 24 V out.
* **Synchronous.** No catch diode, and peak efficiency above 95 % per the datasheet.
* **Few parts.** It is internally compensated, so two resistors set the voltage.
* **The friendliest package a modern synchronous buck comes in.** An 8-pin SOIC
  with 1.27 mm pin pitch and a thermal pad.
* **Low standby current** (24 µA), which matters for anything left wired to a
  battery.
* **A pin-compatible family.** LMR33620 (2 A) and LMR33640 (4 A) drop onto the
  same pads.
* **Price and supply.** Listed active at DigiKey, about \$2.00–2.60 each in single
  quantities.

Prices are from DigiKey's regional listings as shown in search results in
November 2026. DigiKey's site blocks automated access, so I could not check live
stock or build a cart; confirm both when you order. Facts about the chip are from
TI's datasheet (SNVSAN3F), which I read in full.

---

## Circuit

| Part | Job |
|---|---|
| U1 | The regulator: both power switches, controller and compensation |
| C1, C2, C3 | Input capacitors. They sit right at the VIN and PGND pins, because the loop they form with the chip carries the fast switching current |
| C10 | Bulk electrolytic. Damps ringing when the supply arrives over long wires |
| D1 | Optional TVS diode for spikes on the input; also blows the fuse if the input is connected backwards |
| C4 | Bootstrap capacitor for the high-side switch driver |
| C5 | Bypass for the chip's internal 5 V supply |
| L1, C6–C9 | Output filter |
| R1, R2, R3 | Feedback divider. VOUT = 1.0 V × (1 + R1 / (R2 + R3)) |
| R4 | Pulls EN up to VIN so the converter runs with nothing connected to EN |
| R5 | Optional. With R4 it sets a minimum input voltage for turn-on |

---

## Setting the output voltage

This table is printed on the back of every board. R2 and R3 are in series, which
lets ordinary resistor-kit values reach each voltage.

| Output | R1 | R2 | R3 | You get | L1 | C6–C9 |
|---|---|---|---|---|---|---|
| 3.3 V | 100k | 22k | 22k | 3.27 V | 10 µH | 4 × 22 µF 25 V |
| 5 V | 100k | 22k | 2k2 | 5.13 V | 10 µH | 4 × 22 µF 25 V |
| 9 V | 100k | 10k | 2k2 | 9.20 V | 15 µH | 4 × 22 µF 25 V |
| 12 V | 220k | 10k | 10k | 12.00 V | 15 µH | 4 × 22 µF 25 V |
| 24 V | 100k | 2k2 | 2k2 | 23.73 V | 22 µH | 4 × 10 µF 50 V |

All of those resistors are in your kit. Add about ±2.5 % for resistor and
reference tolerance.

**For a more exact voltage**, fit R1 = 100k, a wire link or 0 Ω resistor in R3,
and one 1 % resistor in R2:

| Output | R2 | You get |
|---|---|---|
| 3.3 V | 43k2 | 3.31 V |
| 5 V | 24k9 | 5.02 V |
| 9 V | 12k4 | 9.06 V |
| 12 V | 9k09 | 12.00 V |
| 24 V | 4k32 | 24.15 V |

These five values cost a few cents each, and they are the datasheet's own choices
for 3.3, 5 and 12 V.

For any other voltage: R2 + R3 = R1 / (VOUT − 1). Choose the inductor from the
nearest row, and never go below 0.7 µH per volt of output (datasheet equation 5).

---

## Parts

### From your inventory

| Ref | Value | Inventory | Have | Limits you to |
|---|---|---|---|---|
| R1, R4 | 100k | R-014 | 25 | 12 boards |
| R1 (12 V only) | 220k | R-015 | 25 | |
| R2, R3 | 22k, 10k, 2k2 | R-012, R-011, R-009 | 25, 50, 25 | |
| R3 link (exact option) | 0 Ω | R-001 | 25 | |
| C4 | 100 nF 50 V ceramic | C-021 | 10 | 10 boards |
| C5 | 1 µF 50 V ceramic | C-027 | 10 | 10 boards |
| C10 | 47 µF 50 V or 100 µF 50 V | C-042, C-044 | 8, 6 | 14 boards |
| Pins | 2.54 mm header strip | E-007 | 40 pins | 4 boards |

Two cautions on the kit capacitors. Their dielectric is unverified ("X7R / Y5V"
in the inventory sheet). That is fine on the bench, but Y5V loses most of its
capacitance when hot or cold, so use bought X7R parts for C5 in a vehicle. And
check their lead spacing: the footprints are 5.08 mm, and 2.54 mm parts need their
leads spread.

### To buy

Search DigiKey by these manufacturer part numbers. Quantities are per board.

| Ref | Qty | Part | Part number | Notes |
|---|---|---|---|---|
| U1 | 1 | Buck regulator | TI **LMR33630ADDAR** | [DigiKey listing](https://www.digikey.com/en/products/detail/texas-instruments/LMR33630ADDAR/8554847). Must be the "A" (400 kHz) version in the DDA package |
| L1 | 1 | Inductor 10 µH | Bourns **SRP1265A-100M** | 15.5 A saturation, 13 mΩ. Budget: Bourns SRR1260-100M (5.5 A, 20 mΩ) |
| L1 | 1 | Inductor 15 µH | Bourns **SRP1265A-150M** | 12.5 A, 23 mΩ. Budget: Bourns SRR1260-150M (about 4.6 A, 27 mΩ): under the 5.1 A rule below, so it can saturate in a short circuit before the chip's current limit acts. Fine in normal use |
| L1 | 1 | Inductor 22 µH | Bourns **SRP1265A-220M** | 12 A, 33 mΩ. Or Würth 7447709220 (6.5 A). Not the SRR1260-220M, which saturates at about 3.7 A |
| C1, C2 | 2 | 10 µF 50 V X7R, 1210 | Murata **GRM32ER71H106KA12L** | Or Samsung CL32B106KBJNNNE, TDK C3225X7R1H106K250AC. Also C6–C9 on 24 V builds |
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
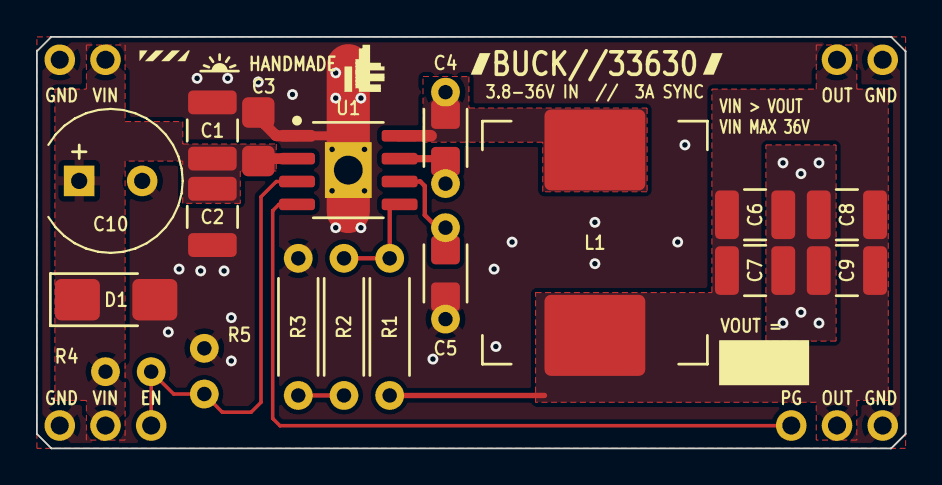
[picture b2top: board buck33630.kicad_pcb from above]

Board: 2 copper layers, 48.3 x 22.9 mm, 22 parts (0 on the bottom side), 10 nets.

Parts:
C1, C2: 10u 50V X7R; C_1210_HandSolder
C3: 220n 50V; C_0805-1206_HandSolder
C4: 100n; C_Dual_THT-P5.08_or_0805-1206
C5: 1u; C_Dual_THT-P5.08_or_0805-1206
C6, C7, C8, C9: COUT; C_1210_HandSolder
C10: 47-100u 50V; CP_Radial_D8.0_P3.5
D1: TVS (opt); D_SMB
J1: IN; PinHeader_1x02_P2.54_Row
J2: IN; PinHeader_1x03_P2.54_Row
J3: OUT; PinHeader_1x02_P2.54_Row
J4: OUT; PinHeader_1x03_P2.54_Row
L1: 10-22uH; L_Universal_10mm-13.5mm
R1: RFBT; R_Axial_0.25W_P7.62_Horizontal
R2: RFBB1; R_Axial_0.25W_P7.62_Horizontal
R3: RFBB2; R_Axial_0.25W_P7.62_Horizontal
R4: 100k; R_Axial_0.25W_P2.54_Vertical
R5: UVLO (opt); R_Axial_0.25W_P2.54_Vertical
U1: LMR33630ADDAR; HSOIC-8-1EP_HandSolder_BackHole

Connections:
BOOT: C4.2, U1.7
EN: J2.3, R4.2, R5.2, U1.3
FB: R1.1, R2.1, U1.5
FBM: R2.2, R3.2
GND: C1.1, C2.2, C3.1, C5.2, C6.2, C7.2, C8.1, C9.1, C10.2, D1.2, J1.1, J2.1, J3.2, J4.3, R3.1, R5.1, U1.1, U1.9
PG: J4.1, U1.4
SW: C4.1, L1.1, U1.8
VCC: C5.1, U1.6
VIN: C1.2, C2.1, C3.2, C10.1, D1.1, J1.2, J2.2, R4.1, U1.2
VOUT: C6.1, C7.1, C8.2, C9.2, J3.1, J4.2, L1.2, R1.2

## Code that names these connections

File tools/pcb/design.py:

"""The task lamp driver board, as data.

This file is the single description of the circuit. The schematic generator
(gen_sch.py) and the board generator (gen_pcb.py) both read it, and check.py
compares what KiCad extracts from each of them against it, so the drawing, the
copper and this list cannot drift apart.

Each part: reference, value, schematic symbol, footprint, {pin number: net},
where it comes from, and a one-line note for the bill of materials.
"""

SYM_QTPY = 'TaskLamp:QTPy_RP2040'
FP_QTPY = 'TaskLamp:QTPy_RP2040_Socket'

FP_R = 'Resistor_THT:R_Axial_DIN0207_L6.3mm_D2.5mm_P10.16mm_Horizontal'
FP_D41 = 'Diode_THT:D_DO-41_SOD81_P10.16mm_Horizontal'
FP_D201 = 'Diode_THT:D_DO-201AD_P15.24mm_Horizontal'
FP_D15 = 'Diode_THT:D_DO-15_P12.70mm_Horizontal'
FP_TO220 = 'Package_TO_SOT_THT:TO-220-3_Vertical'
FP_HSOIC = 'TaskLamp:HSOIC-8-1EP_HandSolder_BackHole'
FP_L7 = 'TaskLamp:L_Bourns_SRP7028A_HandSolder'
FP_C1210 = 'TaskLamp:C_1210_HandSolder'
FP_CCHIP = 'TaskLamp:C_0805-1206_HandSolder'
FP_RCHIP = 'TaskLamp:R_0805-1206_HandSolder'
FP_CDUAL = 'TaskLamp:C_Dual_THT-P5.08_or_0805-1206'
FP_FUSE = 'Fuse:Fuseholder_Blade_Mini_Keystone_3568'
FP_TB = 'TerminalBlock_Phoenix:TerminalBlock_Phoenix_MKDS-1,5-%d-5.08_1x%02d_P5.08mm_Horizontal'
FP_HDR8 = 'Connector_PinHeader_2.54mm:PinHeader_1x08_P2.54mm_Vertical'
FP_CP8 = 'Capacitor_THT:CP_Radial_D8.0mm_P3.50mm'
FP_CP5 = 'Capacitor_THT:CP_Radial_D5.0mm_P2.00mm'
FP_C = 'Capacitor_THT:C_Disc_D5.0mm_W2.5mm_P5.00mm'
FP_TP = 'TestPoint:TestPoint_THTPad_D2.0mm_Drill1.0mm'
FP_HOLE = 'MountingHole:MountingHole_3.2mm_M3'

STOCK = 'stock'   # already in the component inventory
ORDER = 'order'   # on the shopping list (docs/parts-to-order.md)

# Channel order everywhere: R, G, B, warm white, cool white.
CHANNELS = ['R', 'G', 'B', 'WW', 'CW']
CHANNEL_NAMES = {'R': 'red', 'G': 'green', 'B': 'blue', 'WW': 'warm white', 'CW': 'cool white'}

# QT Py pads, numbered like a DIP seen from above with the USB socket at the
# top: 1-7 down the left side, 8-14 up the right side.
QTPY_PINS = {
    '1': ('A0', 'PWM_R'),
    '2': ('A1', 'PWM_G'),
    '3': ('A2', 'PWM_B'),
    '4': ('A3', 'PWM_WW'),
    '5': ('SDA', 'TFT_CS'),
    '6': ('SCL', 'TFT_DC'),
    '7': ('TX', 'PWM_CW'),
    '8': ('RX', 'TFT_LITE'),
    '9': ('SCK', 'TFT_SCK'),
    '10': ('MI', 'ENC_INT'),
    '11': ('MO', 'TFT_MOSI'),
    '12': ('3V', '+3V3'),
    '13': ('GND', 'GND'),
    '14': ('5V', 'QT_5V'),
}

# Display / encoder header, top to bottom on the board.
J4_PINS = ['+3V3', 'TFT_MOSI', 'ENC_INT', 'TFT_SCK', 'TFT_LITE', 'TFT_CS', 'TFT_DC', 'GND']
J4_LABELS = ['3V', 'MOSI', 'INT', 'SCK', 'LITE', 'CS', 'DC', 'GND']


def parts():
    p = []

    def add(ref, value, sym, fp, pins, src, note, mpn=''):
        p.append(dict(ref=ref, value=value, sym=sym, fp=fp, pins=pins, src=src, note=note, mpn=mpn))

    # --- 24 V input: terminal -> fuse -> reverse-polarity diode -> rail
    add('J1', '24V IN', 'Connector:Screw_Terminal_01x02', FP_TB % (2, 2),
        {'1': 'GND', '2': 'VIN'}, ORDER, '24 V supply input, 5.08 mm screw terminal', 'OSTTC022162')
    add('F1', '2A mini blade', 'Device:Fuse', FP_FUSE,
        {'1': 'VFUSE', '2': 'VIN'}, ORDER, 'Mini (ATM) blade fuse holder with a 2 A fuse', '3568 + 0297002.WXNV')
    add('D7', 'SB560', 'Device:D_Schottky', FP_D201,
        {'1': '+24V', '2': 'VFUSE'}, ORDER, 'Reverse-polarity protection, 60 V 5 A Schottky', 'SB560-E3/54')
    add('D8', 'P6KE30A', 'Device:D_Zener', FP_D15,
        {'1': '+24V', '2': 'GND'}, ORDER, 'Surge clamp (TVS) across the 24 V rail', 'P6KE30A')
    add('C1', '100uF 50V', 'Device:C_Polarized', FP_CP8,
        {'1': '+24V', '2': 'GND'}, STOCK, 'Bulk capacitor at the input')
    add('C2', '100uF 50V', 'Device:C_Polarized', FP_CP8,
        {'1': '+24V', '2': 'GND'}, STOCK, 'Bulk capacitor beside the strip terminals')

    # --- 5 V supply for the controller: an LMR33630 buck converter, set for 5.0 V
    # (the circuit of the BUCK//33630 breakout, branch Branchy). EN is tied to VIN, PG unused.
    add('U2', 'LMR33630ADDAR', 'Regulator_Switching:LMR33630ADDA', FP_HSOIC,
        {'1': 'GND', '2': '+24V', '3': '+24V', '5': 'FB', '6': 'VCC', '7': 'BOOT', '8': 'SW', '9': 'GND'},
        ORDER, '24 V to 5 V buck converter, 3 A, 400 kHz', 'LMR33630ADDAR')
    add('L1', '10uH', 'Device:L', FP_L7, {'1': 'SW', '2': '+5V'}, ORDER,
        'Buck inductor, shielded, Isat 6 A', 'SRP7028A-100M')
    add('C3', '10uF 50V', 'Device:C', FP_C1210, {'1': 'GND', '2': '+24V'}, ORDER,
        'Buck input capacitor, X7R', 'GRM32ER71H106KA12L')
    add('C4', '10uF 50V', 'Device:C', FP_C1210, {'1': '+24V', '2': 'GND'}, ORDER,
        'Buck input capacitor, X7R', 'GRM32ER71H106KA12L')
    add('C5', '220nF 50V', 'Device:C', FP_CCHIP, {'1': 'GND', '2': '+24V'}, ORDER,
        'Buck input bypass, X7R 0805 or 1206', 'C0805C224K5RACTU')
    add('C6', '100nF', 'Device:C', FP_CDUAL, {'1': 'SW', '2': 'BOOT'}, STOCK,
        'Bootstrap capacitor (radial, or a chip on the inner pads)')
    add('C7', '1uF', 'Device:C', FP_CDUAL, {'1': 'VCC', '2': 'GND'}, STOCK,
        'Buck VCC capacitor (radial, or a chip on the inner pads)')
    for ref, pins in (('C8', {'1': '+5V', '2': 'GND'}), ('C9', {'1': '+5V', '2': 'GND'}),
                      ('C10', {'1': 'GND', '2': '+5V'}), ('C11', {'1': 'GND', '2': '+5V'})):
        add(ref, '22uF 25V', 'Device:C', FP_C1210, pins, ORDER, 'Buck output capacitor, X7R', 'GRM32ER71E226KE15L')
    add('R11', '100k 1%', 'Device:R', FP_RCHIP, {'1': 'FB', '2': '+5V'}, ORDER,
        'Feedback divider, top (0805 or 1206)', 'RC1206FR-07100KL')
    add('R12', '24.9k 1%', 'Device:R', FP_RCHIP, {'1': 'GND', '2': 'FB'}, ORDER,
        'Feedback divider, bottom: 5.02 V out (0805 or 1206)', 'RC1206FR-0724K9L')
    add('D6', '1N5819', 'Diode:1N5819', FP_D41,
        {'1': 'QT_5V', '2': '+5V'}, STOCK, 'Feeds the QT Py 5V pad; lets USB be plugged in at the same time')

    # --- Controller
    add('U1', 'QT Py RP2040', SYM_QTPY, FP_QTPY,
        {n: net for n, (_, net) in QTPY_PINS.items()}, ORDER,
        'Adafruit QT Py RP2040 on two 1x7 sockets (the board itself is on hand)', '2x PPTC071LFBN-RC')
    add('J4', 'DISPLAY', 'Connector:Conn_01x08_Pin', FP_HDR8,
        {str(i + 1): net for i, net in enumerate(J4_PINS)}, STOCK,
        'Pin header to the TFT and the encoder INT pad')

    # --- Five identical strip switches
    for i, ch in enumerate(CHANNELS):
        n = i + 1
        name = CHANNEL_NAMES[ch]
        add('R%d' % n, '220', 'Device:R', FP_R,
            {'1': 'PWM_' + ch, '2': 'GATE_' + ch}, STOCK, 'Gate resistor, %s' % name)
        add('R%d' % (n + 5), '100k', 'Device:R', FP_R,
            {'1': 'GND', '2': 'GATE_' + ch}, STOCK, 'Gate pull-down, %s' % name)
        add('Q%d' % n, 'IRLB8721', 'Transistor_FET:IRLB8721PBF', FP_TO220,
            {'1': 'GATE_' + ch, '2': 'OUT_' + ch, '3': 'GND'}, STOCK, 'Strip switch, %s' % name)
        add('D%d' % n, '1N5819', 'Diode:1N5819', FP_D41,
            {'1': '+24V', '2': 'OUT_' + ch}, STOCK, 'Clamp for the strip wiring, %s' % name)

    # --- Strip terminals
    add('J3', 'RGB STRIP', 'Connector:Screw_Terminal_01x04', FP_TB % (4, 4),
        {'1': '+24V', '2': 'OUT_R', '3': 'OUT_G', '4': 'OUT_B'}, ORDER,
        'RGB strip: +24 V, red, green, blue', 'OSTTC042162')
    add('J2', 'WHITE STRIP', 'Connector:Screw_Terminal_01x03', FP_TB % (3, 3),
        {'1': '+24V', '2': 'OUT_WW', '3': 'OUT_CW'}, ORDER,
        'Tunable-white strip: +24 V, warm, cool', 'OSTTC032162')

    # --- Test pads and mounting holes
    add('TP1', '+5V', 'Connector:TestPoint', FP_TP, {'1': '+5V'}, '', 'Test pad')
    add('TP2', 'GND', 'Connector:TestPoint', FP_TP, {'1': 'GND'}, '', 'Test pad')
    for n in range(1, 5):
        add('H%d' % n, 'M3', 'Mechanical:MountingHole', FP_HOLE, {}, '', 'Mounting hole, 3.2 mm')
    return p


def netlist():
    """{net name: sorted list of 'REF.pin'} for every pin of every part."""
    nets = {}
    for part in parts():
        for pin, net in part['pins'].items():
            nets.setdefault(net, []).append('%s.%s' % (part['ref'], pin))
    return {k: sorted(v) for k, v in nets.items()}


if __name__ == '__main__':
    ps = parts()
    print('%d parts, %d nets' % (len(ps), len(netlist())))
    for net, pins in sorted(netlist().items()):
        print('  %-9s %s' % (net, ' '.join(pins)))
